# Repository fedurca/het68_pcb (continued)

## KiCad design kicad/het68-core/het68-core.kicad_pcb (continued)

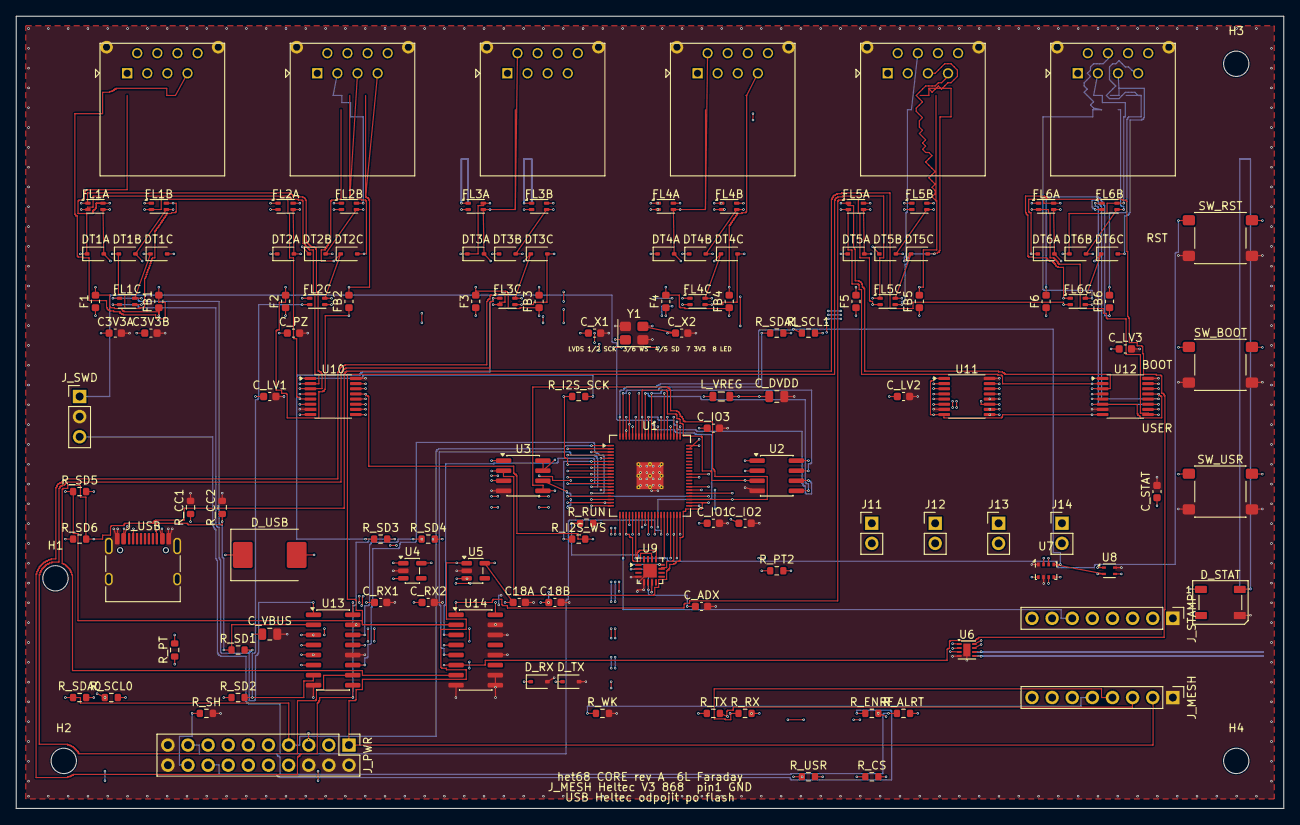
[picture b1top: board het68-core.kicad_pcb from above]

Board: 6 copper layers, 160.0 x 100.0 mm, 134 parts (0 on the bottom side), 156 nets.

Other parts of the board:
H1, H2, H3, H4: M3; MountingHole_3.2mm_M3

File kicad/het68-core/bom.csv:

Ref,Value,Footprint,MPN,LCSC
U1,RP2350B,Package_DFN_QFN:QFN-80-1EP_10x10mm_P0.4mm_EP3.4x3.4mm_ThermalVias,RP2350B,
U2,W25Q128JVSIQ,Package_SO:SOIC-8_3.9x4.9mm_P1.27mm,W25Q128JVSIQ,
U3,APS6404L,Package_SO:SOIC-8_3.9x4.9mm_P1.27mm,APS6404L-3SQR-SN,
Y1,12MHz,Crystal:Crystal_SMD_3225-4Pin_3.2x2.5mm,12MHz 3225,
C_X1,15p,Capacitor_SMD:C_0603_1608Metric,CL10C150JB8NNNC,
C_X2,15p,Capacitor_SMD:C_0603_1608Metric,CL10C150JB8NNNC,
L_VREG,2.2uH,Inductor_SMD:L_0805_2012Metric,2.2uH VREG,
C_DVDD,2.2u,Capacitor_SMD:C_0805_2012Metric,CL21A225KOQNNNE,
U4,AP2112K-3.3,Package_TO_SOT_SMD:SOT-23-5,AP2112K-3.3TRG1,
U5,AP2112K-1.8,Package_TO_SOT_SMD:SOT-23-5,AP2112K-1.8TRG1,C176944
C3V3A,1u,Capacitor_SMD:C_0603_1608Metric,CL10A105KA8NNNC,
C3V3B,100n,Capacitor_SMD:C_0603_1608Metric,CL10B104KB8NNNC,
C18A,1u,Capacitor_SMD:C_0603_1608Metric,CL10A105KA8NNNC,
C18B,100n,Capacitor_SMD:C_0603_1608Metric,CL10B104KB8NNNC,
R_RUN,10k,Resistor_SMD:R_0603_1608Metric,RC0603FR-0710KL,
R_WK,100k,Resistor_SMD:R_0603_1608Metric,RC0603FR-07100KL,
R_CS,10k,Resistor_SMD:R_0603_1608Metric,RC0603FR-0710KL,
R_USR,10k,Resistor_SMD:R_0603_1608Metric,RC0603FR-0710KL,
SW_RST,RESET,Button_Switch_SMD:SW_SPST_PTS645Sx43SMTR92,PTS645SM43SMTR92,
SW_BOOT,BOOT,Button_Switch_SMD:SW_SPST_PTS645Sx43SMTR92,PTS645SM43SMTR92,
SW_USR,USER,Button_Switch_SMD:SW_SPST_PTS645Sx43SMTR92,PTS645SM43SMTR92,
D_STAT,SK6812,LED_SMD:LED_WS2812B_PLCC4_5.0x5.0mm_P3.2mm,"SK6812 (5050, 3.3 V)",
C_STAT,100n,Capacitor_SMD:C_0603_1608Metric,CL10B104KB8NNNC,
J_USB,USB_C,Connector_USB:USB_C_Receptacle_HRO_TYPE-C-31-M-12,TYPE-C-31-M-12,C165948
R_CC1,5.1k,Resistor_SMD:R_0603_1608Metric,RC0603FR-075K1L,
R_CC2,5.1k,Resistor_SMD:R_0603_1608Metric,RC0603FR-075K1L,
D_USB,SS34,Diode_SMD:D_SMC,SS34,
C_VBUS,10u,Capacitor_SMD:C_0805_2012Metric,CL21A106KOQNNNE,
J_MESH,J_MESH,Connector_PinHeader_2.54mm:PinHeader_1x08_P2.54mm_Vertical,PinHeader 1x8 Heltec V3,
J_STAMP,J_STAMP_DNP,Connector_PinHeader_2.54mm:PinHeader_1x08_P2.54mm_Vertical,DNP stamp RAK class,
R_TX,22,Resistor_SMD:R_0603_1608Metric,RC0603FR-0722RL,
R_RX,22,Resistor_SMD:R_0603_1608Metric,RC0603FR-0722RL,
R_I2S_SCK,33,Resistor_SMD:R_0603_1608Metric,RC0603FR-0733RL,
R_I2S_WS,33,Resistor_SMD:R_0603_1608Metric,RC0603FR-0733RL,
D_TX,PESD5V0X1BT,Diode_SMD:D_SOD-323,PESD5V0X1BT,
D_RX,PESD5V0X1BT,Diode_SMD:D_SOD-323,PESD5V0X1BT,
J_SWD,SWD,Connector_PinHeader_2.54mm:PinHeader_1x03_P2.54mm_Vertical,SWD,
J_PWR,J_PWR,Connector_PinHeader_2.54mm:PinHeader_2x10_P2.54mm_Vertical,interconnect 2x10,
R_SDA0,4.7k,Resistor_SMD:R_0603_1608Metric,RC0603FR-074K7L,
R_SCL0,4.7k,Resistor_SMD:R_0603_1608Metric,RC0603FR-074K7L,
R_SDA1,4.7k,Resistor_SMD:R_0603_1608Metric,RC0603FR-074K7L,
R_SCL1,4.7k,Resistor_SMD:R_0603_1608Metric,RC0603FR-074K7L,
R_PT,1k,Resistor_SMD:R_0603_1608Metric,RC0603FR-071KL,
R_PT2,0,Resistor_SMD:R_0603_1608Metric,RC0603FR-070RL,
R_SH,0,Resistor_SMD:R_0603_1608Metric,RC0603FR-070RL,
R_ENRF,10k,Resistor_SMD:R_0603_1608Metric,RC0603FR-0710KL,
R_ALRT,10k,Resistor_SMD:R_0603_1608Metric,RC0603FR-0710KL,
U7,DPS310,Package_LGA:Bosch_LGA-8_2x2.5mm_P0.65mm_ClockwisePinNumbering,DPS310,C130156
U8,SHT40,Sensor_Humidity:Sensirion_DFN-4_1.5x1.5mm_P0.8mm_SHT4x_NoCentralPad,SHT40-AD1B-R2,C2909890
U9,ADXL355,Package_DFN_QFN:QFN-16-1EP_3x3mm_P0.5mm_EP1.7x1.7mm,ADXL355BCCZ,
C_ADX,100n,Capacitor_SMD:C_0603_1608Metric,CL10B104KB8NNNC,
U6,DRV8837C,Package_SON:Texas_DSG0008A_WSON-8-1EP_2x2mm_P0.5mm_EP0.9x1.6mm,DRV8837CDSGR,C191000
C_PZ,100n,Capacitor_SMD:C_0603_1608Metric,CL10B104KB8NNNC,
J11,PZ1,Connector_PinHeader_2.54mm:PinHeader_1x02_P2.54mm_Vertical,PS1240,
J12,PZ2,Connector_PinHeader_2.54mm:PinHeader_1x02_P2.54mm_Vertical,PS1240,
J13,PZ3,Connector_PinHeader_2.54mm:PinHeader_1x02_P2.54mm_Vertical,PS1240,
J14,PZ4,Connector_PinHeader_2.54mm:PinHeader_1x02_P2.54mm_Vertical,PS1240,
U10,SN65LVDS047,Package_SO:TSSOP-16_4.4x5mm_P0.65mm,SN65LVDS047PW,
C_LV1,100n,Capacitor_SMD:C_0603_1608Metric,CL10B104KB8NNNC,
U11,SN65LVDS047,Package_SO:TSSOP-16_4.4x5mm_P0.65mm,SN65LVDS047PW,
C_LV2,100n,Capacitor_SMD:C_0603_1608Metric,CL10B104KB8NNNC,
U12,SN65LVDS047,Package_SO:TSSOP-16_4.4x5mm_P0.65mm,SN65LVDS047PW,
C_LV3,100n,Capacitor_SMD:C_0603_1608Metric,CL10B104KB8NNNC,
U13,SN65LVDS32,Package_SO:SOIC-16_3.9x9.9mm_P1.27mm,SN65LVDS32D,
U14,SN65LVDS32,Package_SO:SOIC-16_3.9x9.9mm_P1.27mm,SN65LVDS32D,
C_RX1,100n,Capacitor_SMD:C_0603_1608Metric,CL10B104KB8NNNC,
C_RX2,100n,Capacitor_SMD:C_0603_1608Metric,CL10B104KB8NNNC,
J1,MIC1,het68:RJ45_Vertical_het68,RJ45-8P8C-VERT,
FL1A,CMC,Inductor_SMD:L_CommonModeChoke_Coilank_ACM2012,ACM2012,
FL1B,CMC,Inductor_SMD:L_CommonModeChoke_Coilank_ACM2012,ACM2012,
FL1C,CMC,Inductor_SMD:L_CommonModeChoke_Coilank_ACM2012,ACM2012,
DT1A,PESD5V0X1BT,Diode_SMD:D_SOD-323,PESD5V0X1BT,
DT1B,PESD5V0X1BT,Diode_SMD:D_SOD-323,PESD5V0X1BT,
DT1C,PESD5V0X1BT,Diode_SMD:D_SOD-323,PESD5V0X1BT,
R_SD1,100,Resistor_SMD:R_0603_1608Metric,RC0603FR-07100RL,
F1,0.25A,Fuse:Fuse_0603_1608Metric,PPTC 0603,
FB1,600R,Inductor_SMD:L_0603_1608Metric,BLM18PG601SN1D,
J2,MIC2,het68:RJ45_Vertical_het68,RJ45-8P8C-VERT,
FL2A,CMC,Inductor_SMD:L_CommonModeChoke_Coilank_ACM2012,ACM2012,
FL2B,CMC,Inductor_SMD:L_CommonModeChoke_Coilank_ACM2012,ACM2012,
FL2C,CMC,Inductor_SMD:L_CommonModeChoke_Coilank_ACM2012,ACM2012,
DT2A,PESD5V0X1BT,Diode_SMD:D_SOD-323,PESD5V0X1BT,
DT2B,PESD5V0X1BT,Diode_SMD:D_SOD-323,PESD5V0X1BT,
DT2C,PESD5V0X1BT,Diode_SMD:D_SOD-323,PESD5V0X1BT,
R_SD2,100,Resistor_SMD:R_0603_1608Metric,RC0603FR-07100RL,
F2,0.25A,Fuse:Fuse_0603_1608Metric,PPTC 0603,
FB2,600R,Inductor_SMD:L_0603_1608Metric,BLM18PG601SN1D,
J3,MIC3,het68:RJ45_Vertical_het68,RJ45-8P8C-VERT,
FL3A,CMC,Inductor_SMD:L_CommonModeChoke_Coilank_ACM2012,ACM2012,
FL3B,CMC,Inductor_SMD:L_CommonModeChoke_Coilank_ACM2012,ACM2012,
FL3C,CMC,Inductor_SMD:L_CommonModeChoke_Coilank_ACM2012,ACM2012,
DT3A,PESD5V0X1BT,Diode_SMD:D_SOD-323,PESD5V0X1BT,
DT3B,PESD5V0X1BT,Diode_SMD:D_SOD-323,PESD5V0X1BT,
DT3C,PESD5V0X1BT,Diode_SMD:D_SOD-323,PESD5V0X1BT,
R_SD3,100,Resistor_SMD:R_0603_1608Metric,RC0603FR-07100RL,
F3,0.25A,Fuse:Fuse_0603_1608Metric,PPTC 0603,
FB3,600R,Inductor_SMD:L_0603_1608Metric,BLM18PG601SN1D,
J4,MIC4,het68:RJ45_Vertical_het68,RJ45-8P8C-VERT,
FL4A,CMC,Inductor_SMD:L_CommonModeChoke_Coilank_ACM2012,ACM2012,
FL4B,CMC,Inductor_SMD:L_CommonModeChoke_Coilank_ACM2012,ACM2012,
FL4C,CMC,Inductor_SMD:L_CommonModeChoke_Coilank_ACM2012,ACM2012,
DT4A,PESD5V0X1BT,Diode_SMD:D_SOD-323,PESD5V0X1BT,
DT4B,PESD5V0X1BT,Diode_SMD:D_SOD-323,PESD5V0X1BT,
DT4C,PESD5V0X1BT,Diode_SMD:D_SOD-323,PESD5V0X1BT,
R_SD4,100,Resistor_SMD:R_0603_1608Metric,RC0603FR-07100RL,
F4,0.25A,Fuse:Fuse_0603_1608Metric,PPTC 0603,
FB4,600R,Inductor_SMD:L_0603_1608Metric,BLM18PG601SN1D,
J5,MIC5,het68:RJ45_Vertical_het68,RJ45-8P8C-VERT,
FL5A,CMC,Inductor_SMD:L_CommonModeChoke_Coilank_ACM2012,ACM2012,
FL5B,CMC,Inductor_SMD:L_CommonModeChoke_Coilank_ACM2012,ACM2012,
FL5C,CMC,Inductor_SMD:L_CommonModeChoke_Coilank_ACM2012,ACM2012,
DT5A,PESD5V0X1BT,Diode_SMD:D_SOD-323,PESD5V0X1BT,
DT5B,PESD5V0X1BT,Diode_SMD:D_SOD-323,PESD5V0X1BT,
DT5C,PESD5V0X1BT,Diode_SMD:D_SOD-323,PESD5V0X1BT,
R_SD5,100,Resistor_SMD:R_0603_1608Metric,RC0603FR-07100RL,
F5,0.25A,Fuse:Fuse_0603_1608Metric,PPTC 0603,
FB5,600R,Inductor_SMD:L_0603_1608Metric,BLM18PG601SN1D,
J6,MIC6,het68:RJ45_Vertical_het68,RJ45-8P8C-VERT,
FL6A,CMC,Inductor_SMD:L_CommonModeChoke_Coilank_ACM2012,ACM2012,
FL6B,CMC,Inductor_SMD:L_CommonModeChoke_Coilank_ACM2012,ACM2012,
FL6C,CMC,Inductor_SMD:L_CommonModeChoke_Coilank_ACM2012,ACM2012,
DT6A,PESD5V0X1BT,Diode_SMD:D_SOD-323,PESD5V0X1BT,
DT6B,PESD5V0X1BT,Diode_SMD:D_SOD-323,PESD5V0X1BT,
DT6C,PESD5V0X1BT,Diode_SMD:D_SOD-323,PESD5V0X1BT,
R_SD6,100,Resistor_SMD:R_0603_1608Metric,RC0603FR-07100RL,
F6,0.25A,Fuse:Fuse_0603_1608Metric,PPTC 0603,
FB6,600R,Inductor_SMD:L_0603_1608Metric,BLM18PG601SN1D,
C_IO1,100n,Capacitor_SMD:C_0603_1608Metric,CL10B104KB8NNNC,
C_IO2,100n,Capacitor_SMD:C_0603_1608Metric,CL10B104KB8NNNC,
C_IO3,1u,Capacitor_SMD:C_0603_1608Metric,CL10A105KA8NNNC,

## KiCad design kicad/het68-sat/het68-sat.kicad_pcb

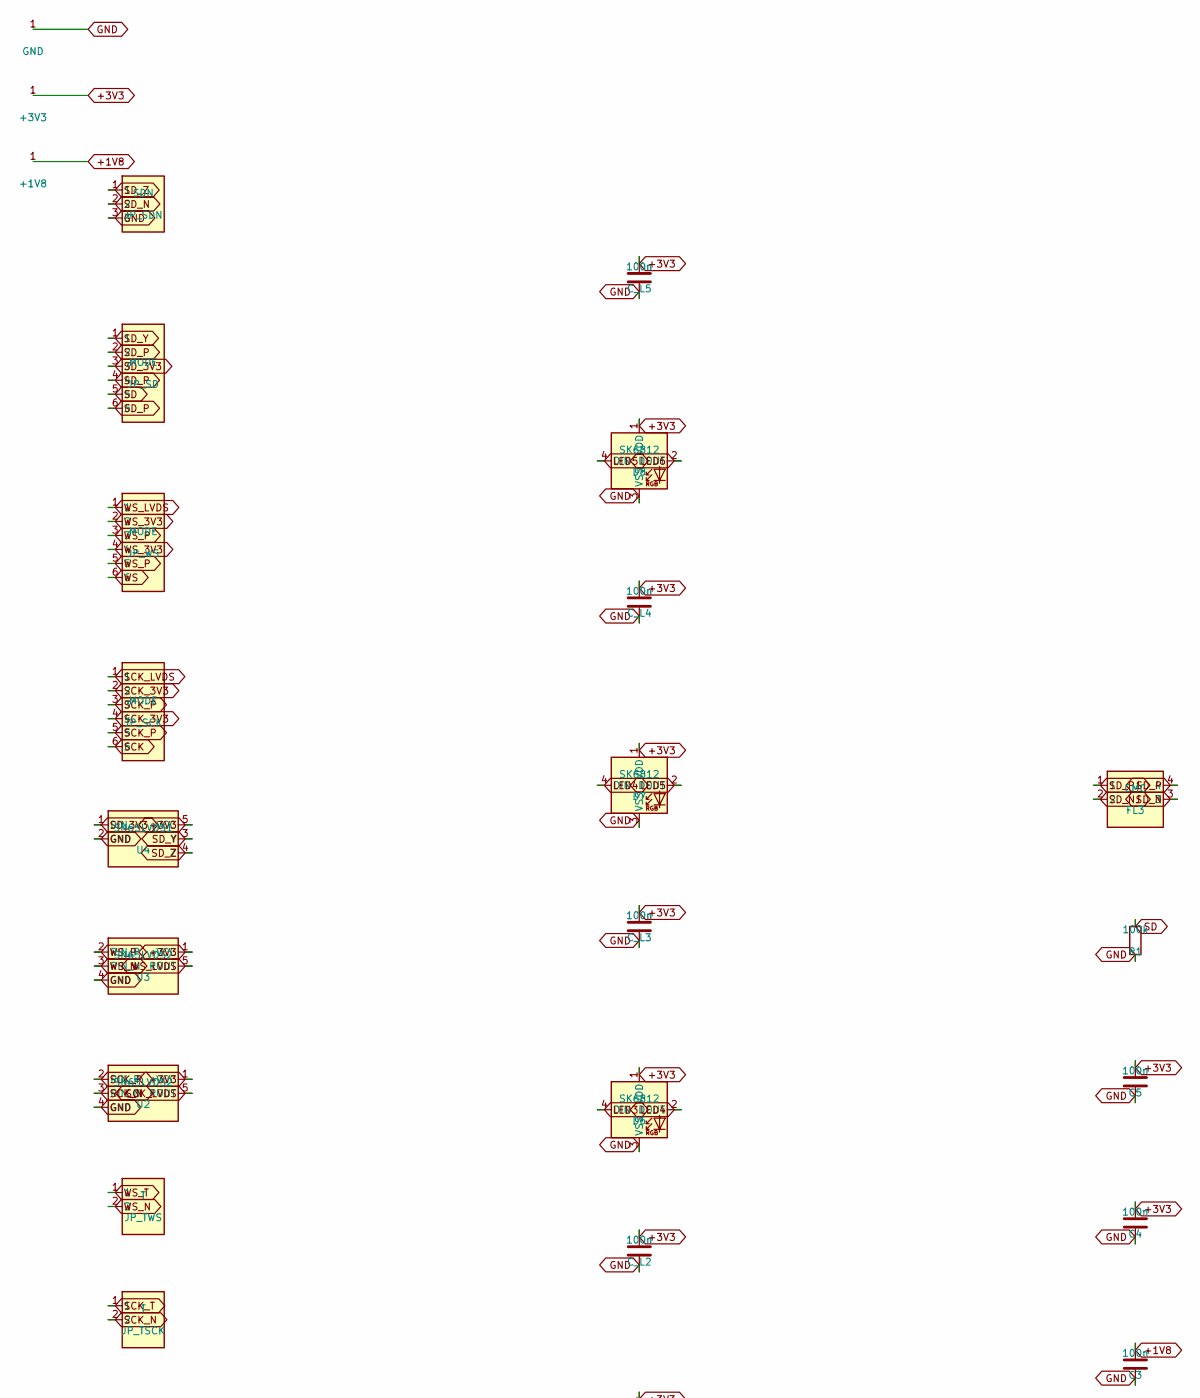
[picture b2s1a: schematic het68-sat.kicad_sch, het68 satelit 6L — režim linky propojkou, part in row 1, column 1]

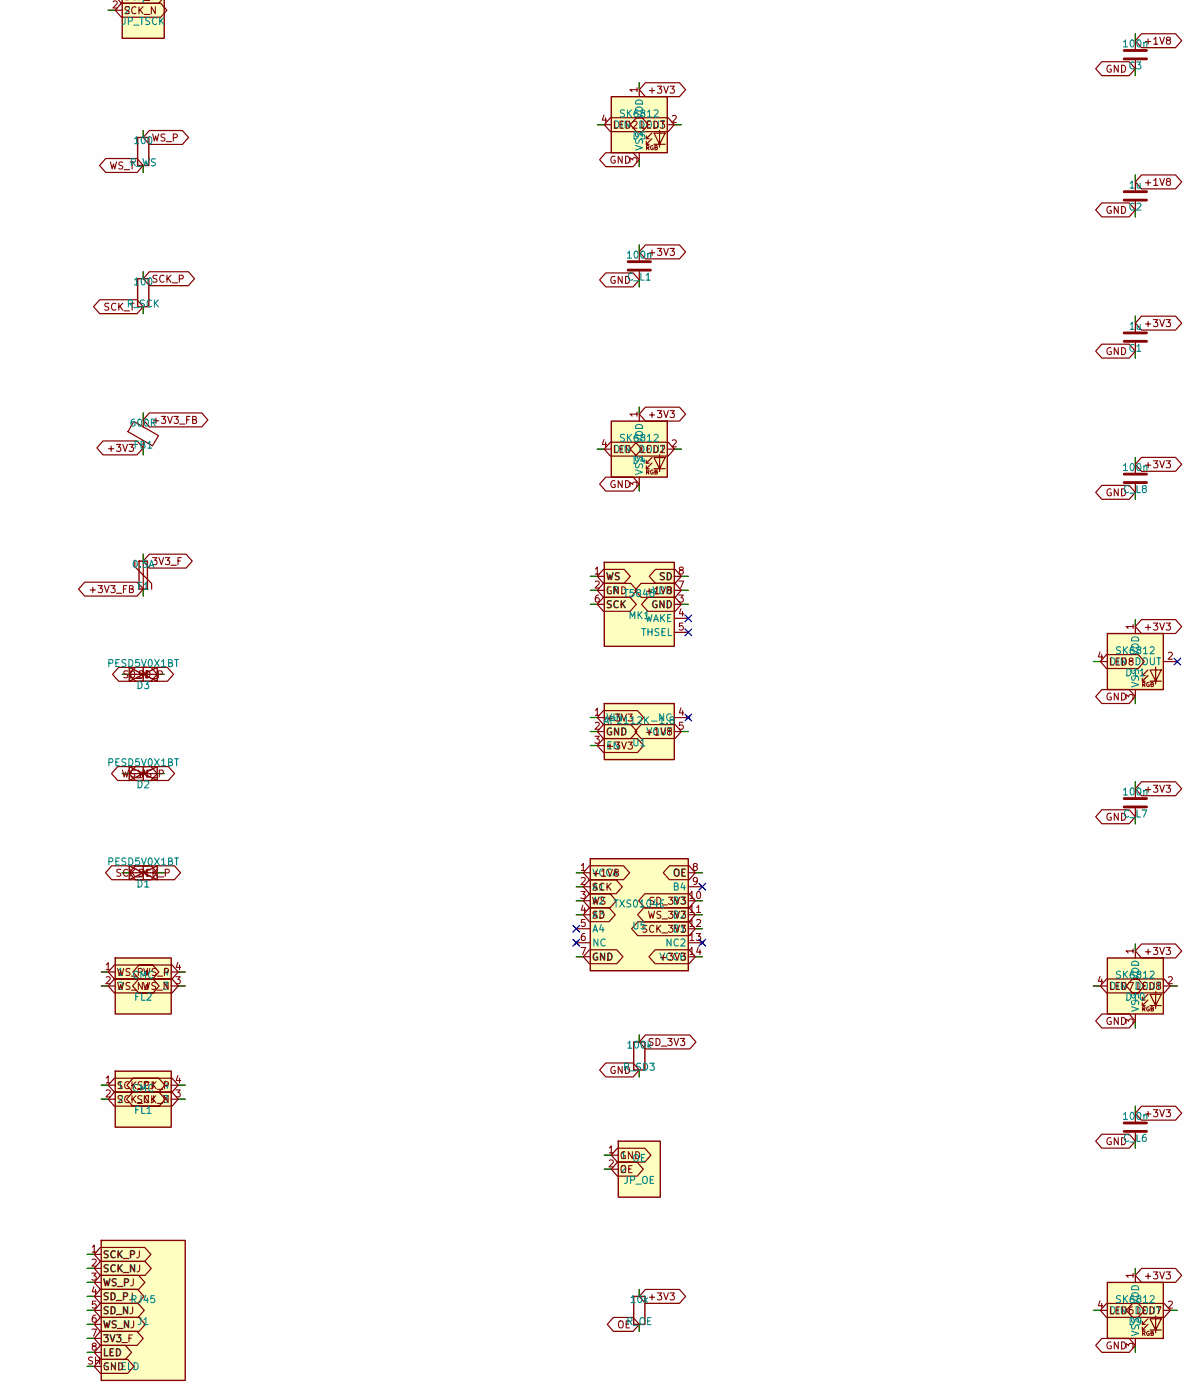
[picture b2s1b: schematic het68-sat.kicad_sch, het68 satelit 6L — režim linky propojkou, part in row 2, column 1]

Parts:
C1, C2: 1u; C_0603_1608Metric; MPN CL10A105KA8NNNC
C3, C4, C5: 100n; C_0603_1608Metric; MPN CL10B104KB8NNNC
C_L1, C_L2, C_L3, C_L4, C_L5, C_L6, C_L7, C_L8: 100n; C_0603_1608Metric; MPN CL10B104KB8NNNC
D1, D2, D3: PESD5V0X1BT; D_SOD-323; MPN PESD5V0X1BT
D4, D5, D6, D7, D8, D9, D10, D11: SK6812; LED_WS2812B_PLCC4_5.0x5.0mm_P3.2mm; MPN SK6812 (5050, 3.3 V)
F1: 0.5A; Fuse_0603_1608Metric; MPN PPTC 0603
FB1: 600R; L_0603_1608Metric; MPN BLM18PG601SN1D
FL1, FL2, FL3: CMC; L_CommonModeChoke_Coilank_ACM2012; MPN ACM2012
J1: RJ45; RJ45_Vertical_het68; MPN RJ45-8P8C-VERT
JP_OE: OE; PinHeader_1x02_P2.54mm_Vertical; MPN jumper OE to GND = 1V8 mode
JP_SCK: MODE; PinHeader_2x03_P2.54mm_Vertical; MPN SCK radky DIFF / 3V3 / 1V8
JP_SD: MODE; PinHeader_2x03_P2.54mm_Vertical; MPN SD radky DIFF / 3V3 / 1V8
JP_SDN: SDN; PinHeader_1x03_P2.54mm_Vertical; MPN jumper SDN 1-2 DIFF 2-3 single-ended
JP_TSCK: T; PinHeader_1x02_P2.54mm_Vertical; MPN jumper DIFF term SCK
JP_TWS: T; PinHeader_1x02_P2.54mm_Vertical; MPN jumper DIFF term WS
JP_WS: MODE; PinHeader_2x03_P2.54mm_Vertical; MPN WS radky DIFF / 3V3 / 1V8
MK1: T5848; MPN MMICT5848-00-012
R1: 100k; R_0603_1608Metric; MPN RC0603FR-07100KL
R_OE: 10k; R_0603_1608Metric; MPN RC0603FR-0710KL
R_SCK: 100; R_0603_1608Metric; MPN RC0603FR-07100RL
R_SD3: 100k; R_0603_1608Metric; MPN RC0603FR-07100KL
R_WS: 100; R_0603_1608Metric; MPN RC0603FR-07100RL
U1: AP2112K-1.8; SOT-23-5; MPN AP2112K-1.8TRG1
U2, U3: SN65LVDS2; SOT-23-5; MPN SN65LVDS2DBVR
U4: SN65LVDS1; SOT-23-5; MPN SN65LVDS1DBVR
U5: TXS0104E; SOIC-14_3.9x8.7mm_P1.27mm; MPN TXS0104EDR

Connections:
3V3_F: F1.1, J1.7 (3V3)
+1V8: C2.1, C3.1, MK1.7 (VDD), U1.5 (VOUT), U5.1 (VCCA)
+3V3: C1.1, C4.1, C5.1, C_L1.1, C_L2.1, C_L3.1, C_L4.1, C_L5.1, C_L6.1, C_L7.1, C_L8.1, D4.1 (VDD), D5.1 (VDD), D6.1 (VDD), D7.1 (VDD), D8.1 (VDD), D9.1 (VDD), D10.1 (VDD), D11.1 (VDD), FB1.2, R_OE.1, U1.1 (VIN), U1.3 (EN), U2.1 (VCC), U3.1 (VCC), U4.5 (VCC), U5.14 (VCCB)
+3V3_FB: F1.2, FB1.1
GND: C1.2, C2.2, C3.2, C4.2, C5.2, C_L1.2, C_L2.2, C_L3.2, C_L4.2, C_L5.2, C_L6.2, C_L7.2, C_L8.2, D4.3 (VSS), D5.3 (VSS), D6.3 (VSS), D7.3 (VSS), D8.3 (VSS), D9.3 (VSS), D10.3 (VSS), D11.3 (VSS), J1.SH (SHIELD), JP_OE.1, JP_SDN.3, MK1.2 (LR), MK1.3 (GND), R1.2, R_SD3.2, U1.2 (GND), U2.4 (GND), U3.4 (GND), U4.2 (GND), U5.7 (GND)
LED: D4.4 (DIN), J1.8 (LED)
LED2: D4.2 (DOUT), D5.4 (DIN)
LED3: D5.2 (DOUT), D6.4 (DIN)
LED4: D6.2 (DOUT), D7.4 (DIN)
LED5: D7.2 (DOUT), D8.4 (DIN)
LED6: D8.2 (DOUT), D9.4 (DIN)
LED7: D9.2 (DOUT), D10.4 (DIN)
LED8: D10.2 (DOUT), D11.4 (DIN)
OE: JP_OE.2, R_OE.2, U5.8 (OE)
SCK: JP_SCK.6, MK1.6 (SCK), U5.2 (A1)
SCK_3V3: JP_SCK.2, JP_SCK.4, U5.12 (B1)
SCK_LVDS: JP_SCK.1, U2.5 (ROUT)
SCK_N: D1.2 (A2), FL1.3, JP_TSCK.2, U2.3 (RIN_N)
SCK_NJ: FL1.2, J1.2 (SCK_N)
SCK_P: D1.1 (A1), FL1.4, JP_SCK.3, JP_SCK.5, R_SCK.1, U2.2 (RIN_P)
SCK_PJ: FL1.1, J1.1 (SCK_P)
SCK_T: JP_TSCK.1, R_SCK.2
SD: JP_SD.5, MK1.8 (SD), R1.1, U5.4 (A3)
SD_3V3: JP_SD.3, R_SD3.1, U4.1 (DIN), U5.10 (B3)
SD_N: D3.2 (A2), FL3.3, JP_SDN.2
SD_NJ: FL3.2, J1.5 (SD_N)
SD_P: D3.1 (A1), FL3.4, JP_SD.2, JP_SD.4, JP_SD.6
SD_PJ: FL3.1, J1.4 (SD_P)
SD_Y: JP_SD.1, U4.3 (Y)
SD_Z: JP_SDN.1, U4.4 (Z)
WS: JP_WS.6, MK1.1 (WS), U5.3 (A2)
WS_3V3: JP_WS.2, JP_WS.4, U5.11 (B2)
WS_LVDS: JP_WS.1, U3.5 (ROUT)
WS_N: D2.2 (A2), FL2.3, JP_TWS.2, U3.3 (RIN_N)
WS_NJ: FL2.2, J1.6 (WS_N)
WS_P: D2.1 (A1), FL2.4, JP_WS.3, JP_WS.5, R_WS.1, U3.2 (RIN_P)
WS_PJ: FL2.1, J1.3 (WS_P)
WS_T: JP_TWS.1, R_WS.2

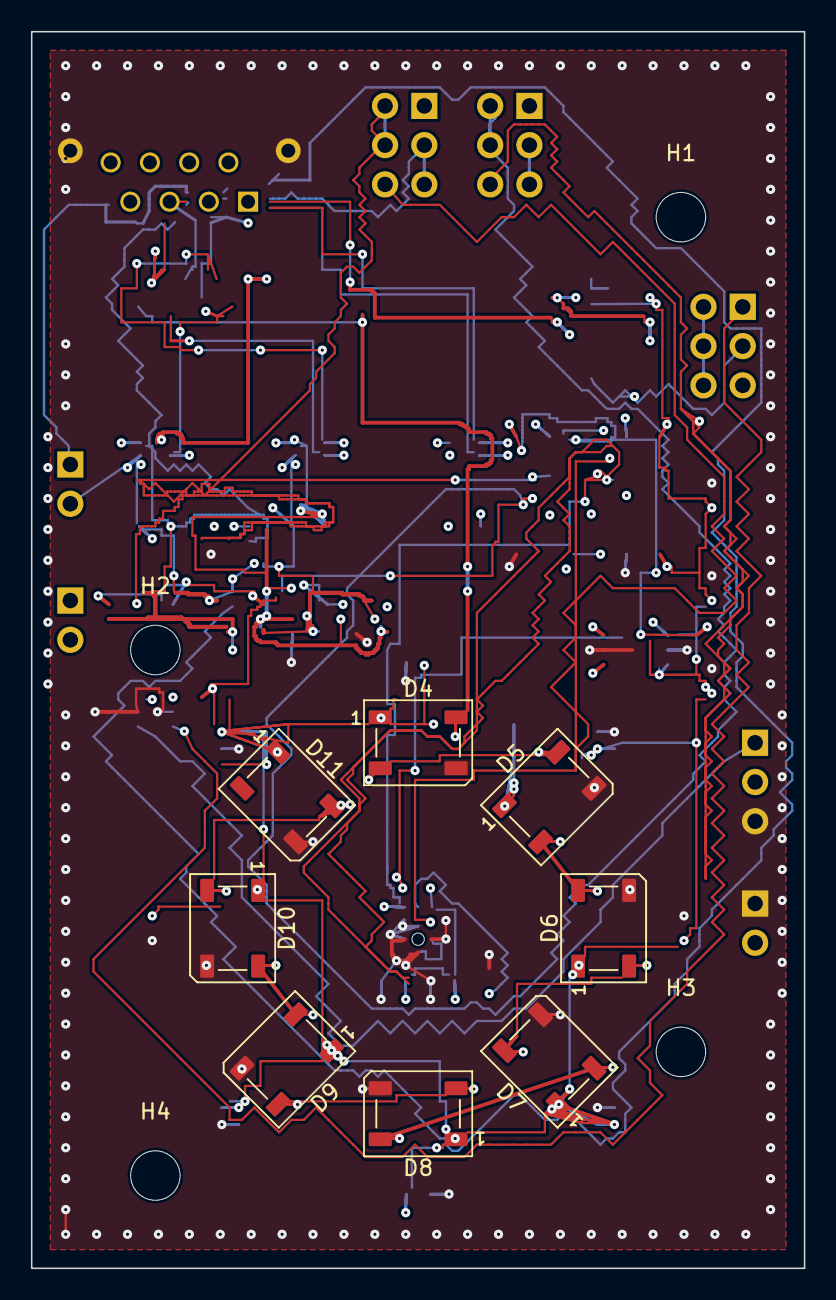
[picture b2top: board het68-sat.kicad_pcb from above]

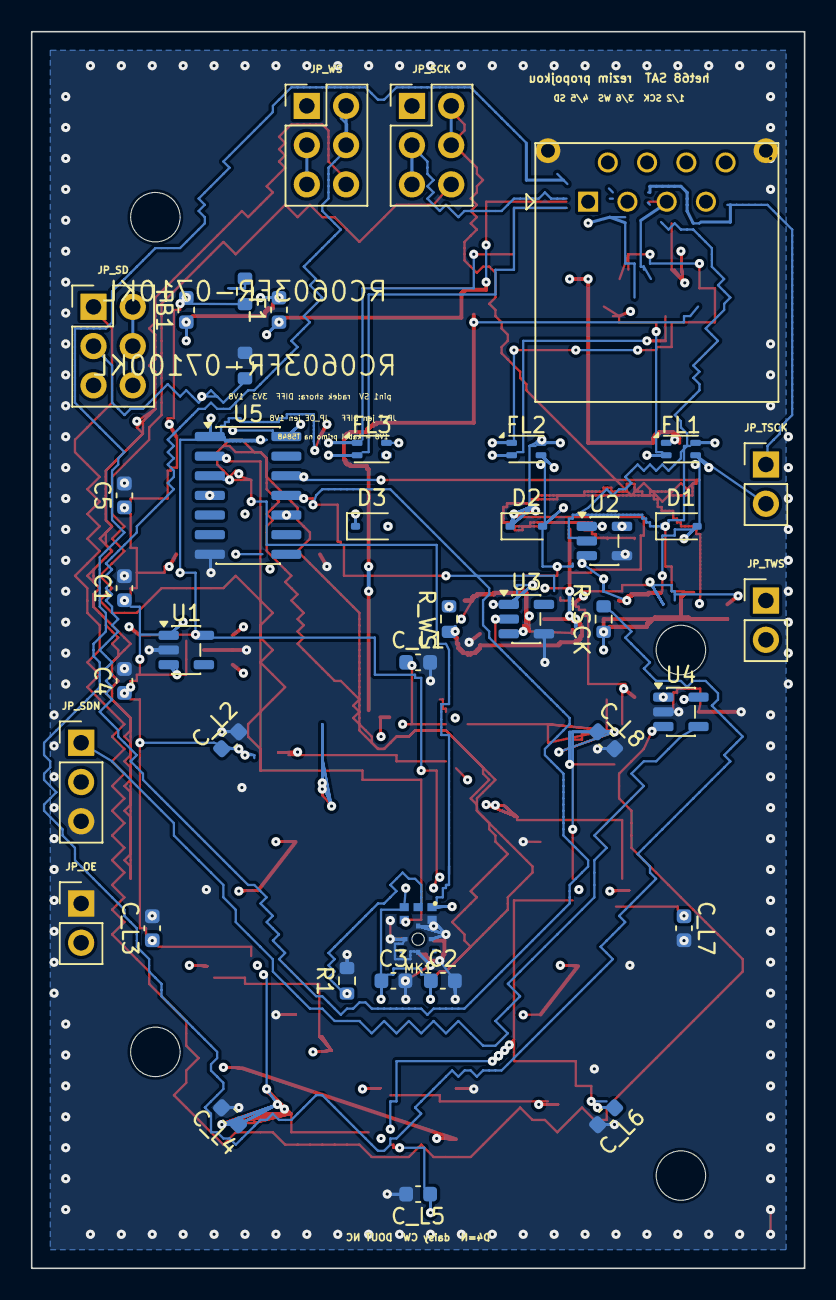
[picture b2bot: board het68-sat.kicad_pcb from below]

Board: 6 copper layers, 50.0 x 80.0 mm, 52 parts (40 on the bottom side), 38 nets.

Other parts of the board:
H1, H2, H3, H4: M3; MountingHole_3.2mm_M3

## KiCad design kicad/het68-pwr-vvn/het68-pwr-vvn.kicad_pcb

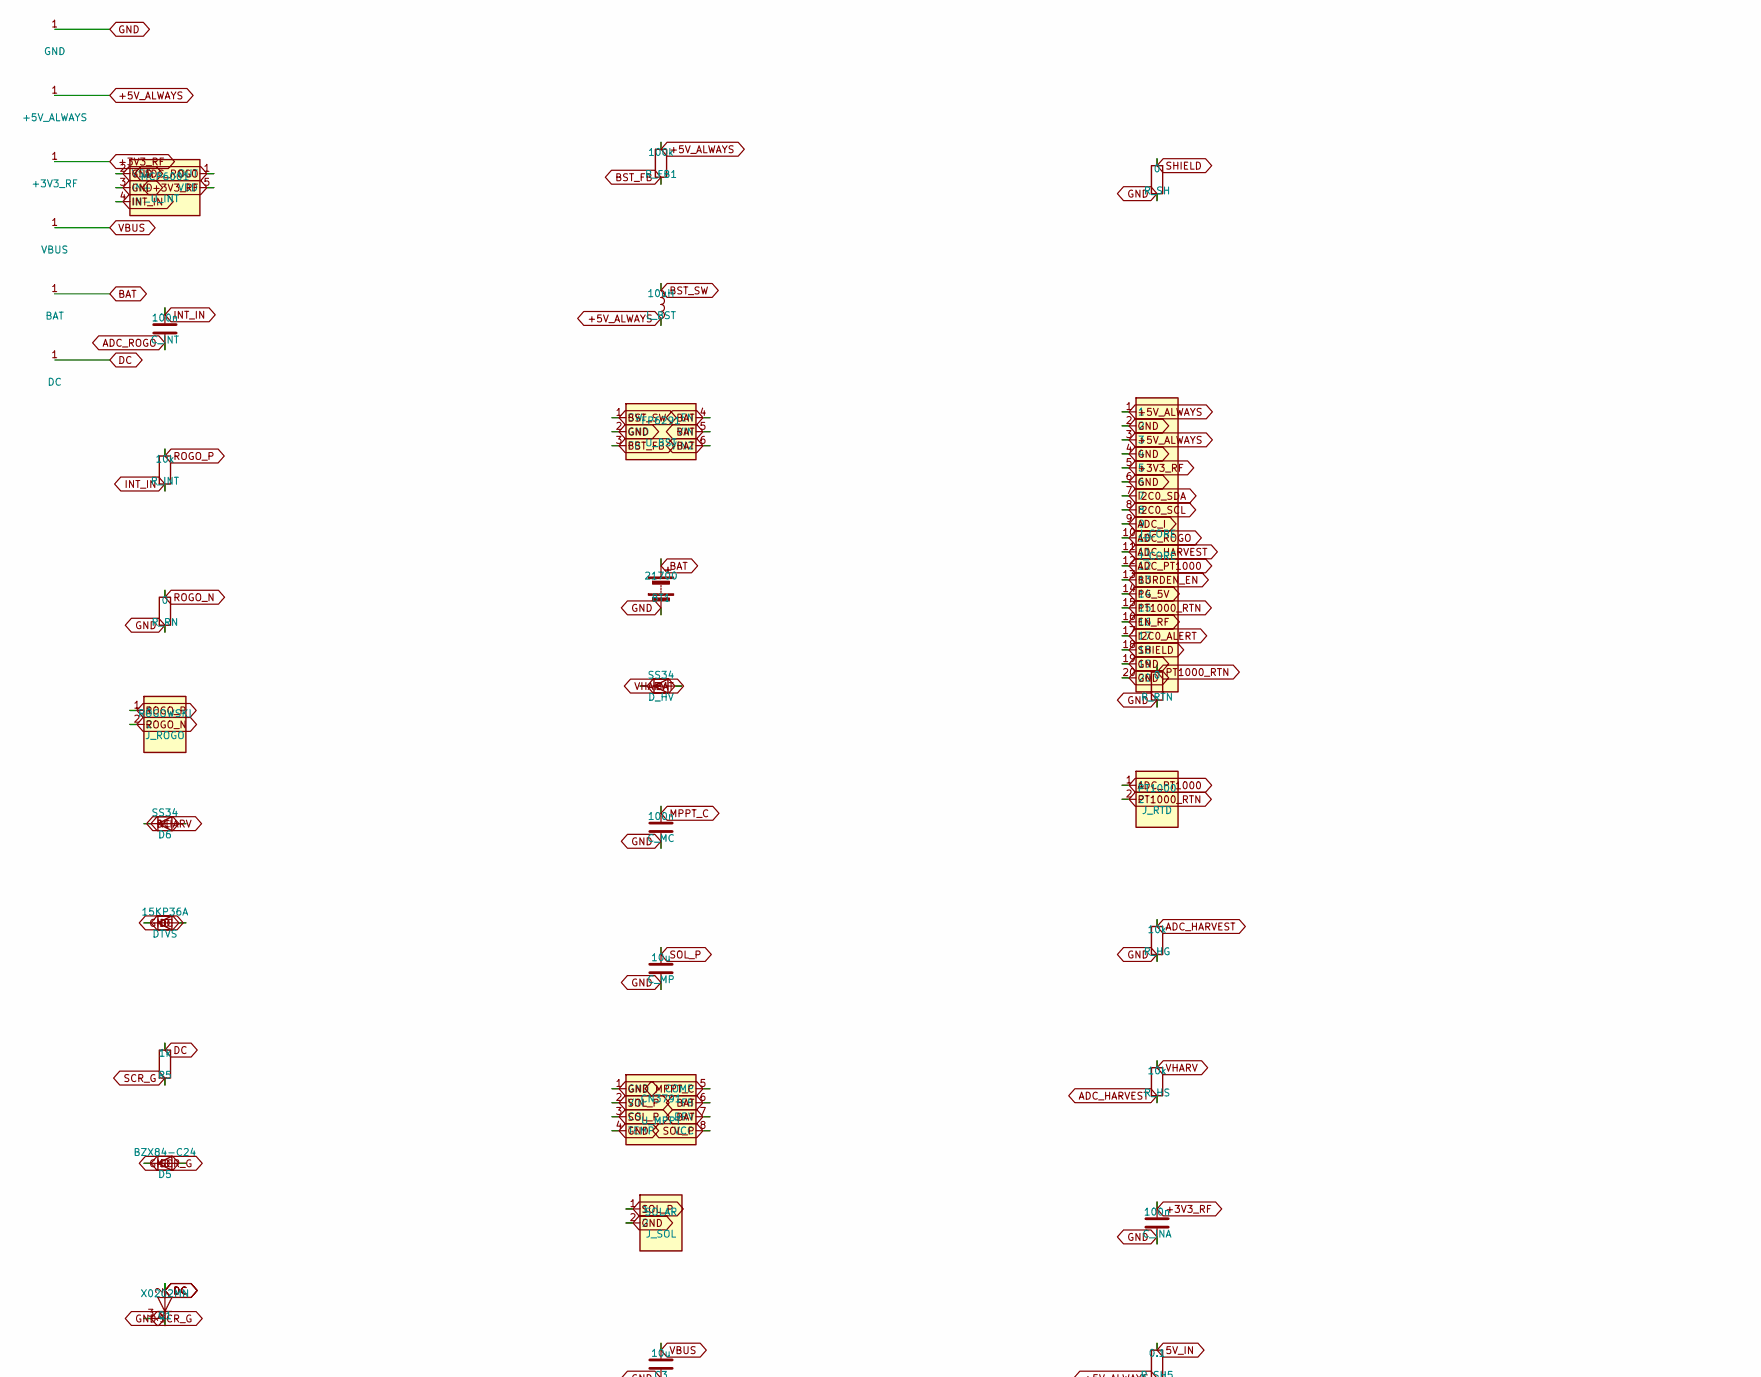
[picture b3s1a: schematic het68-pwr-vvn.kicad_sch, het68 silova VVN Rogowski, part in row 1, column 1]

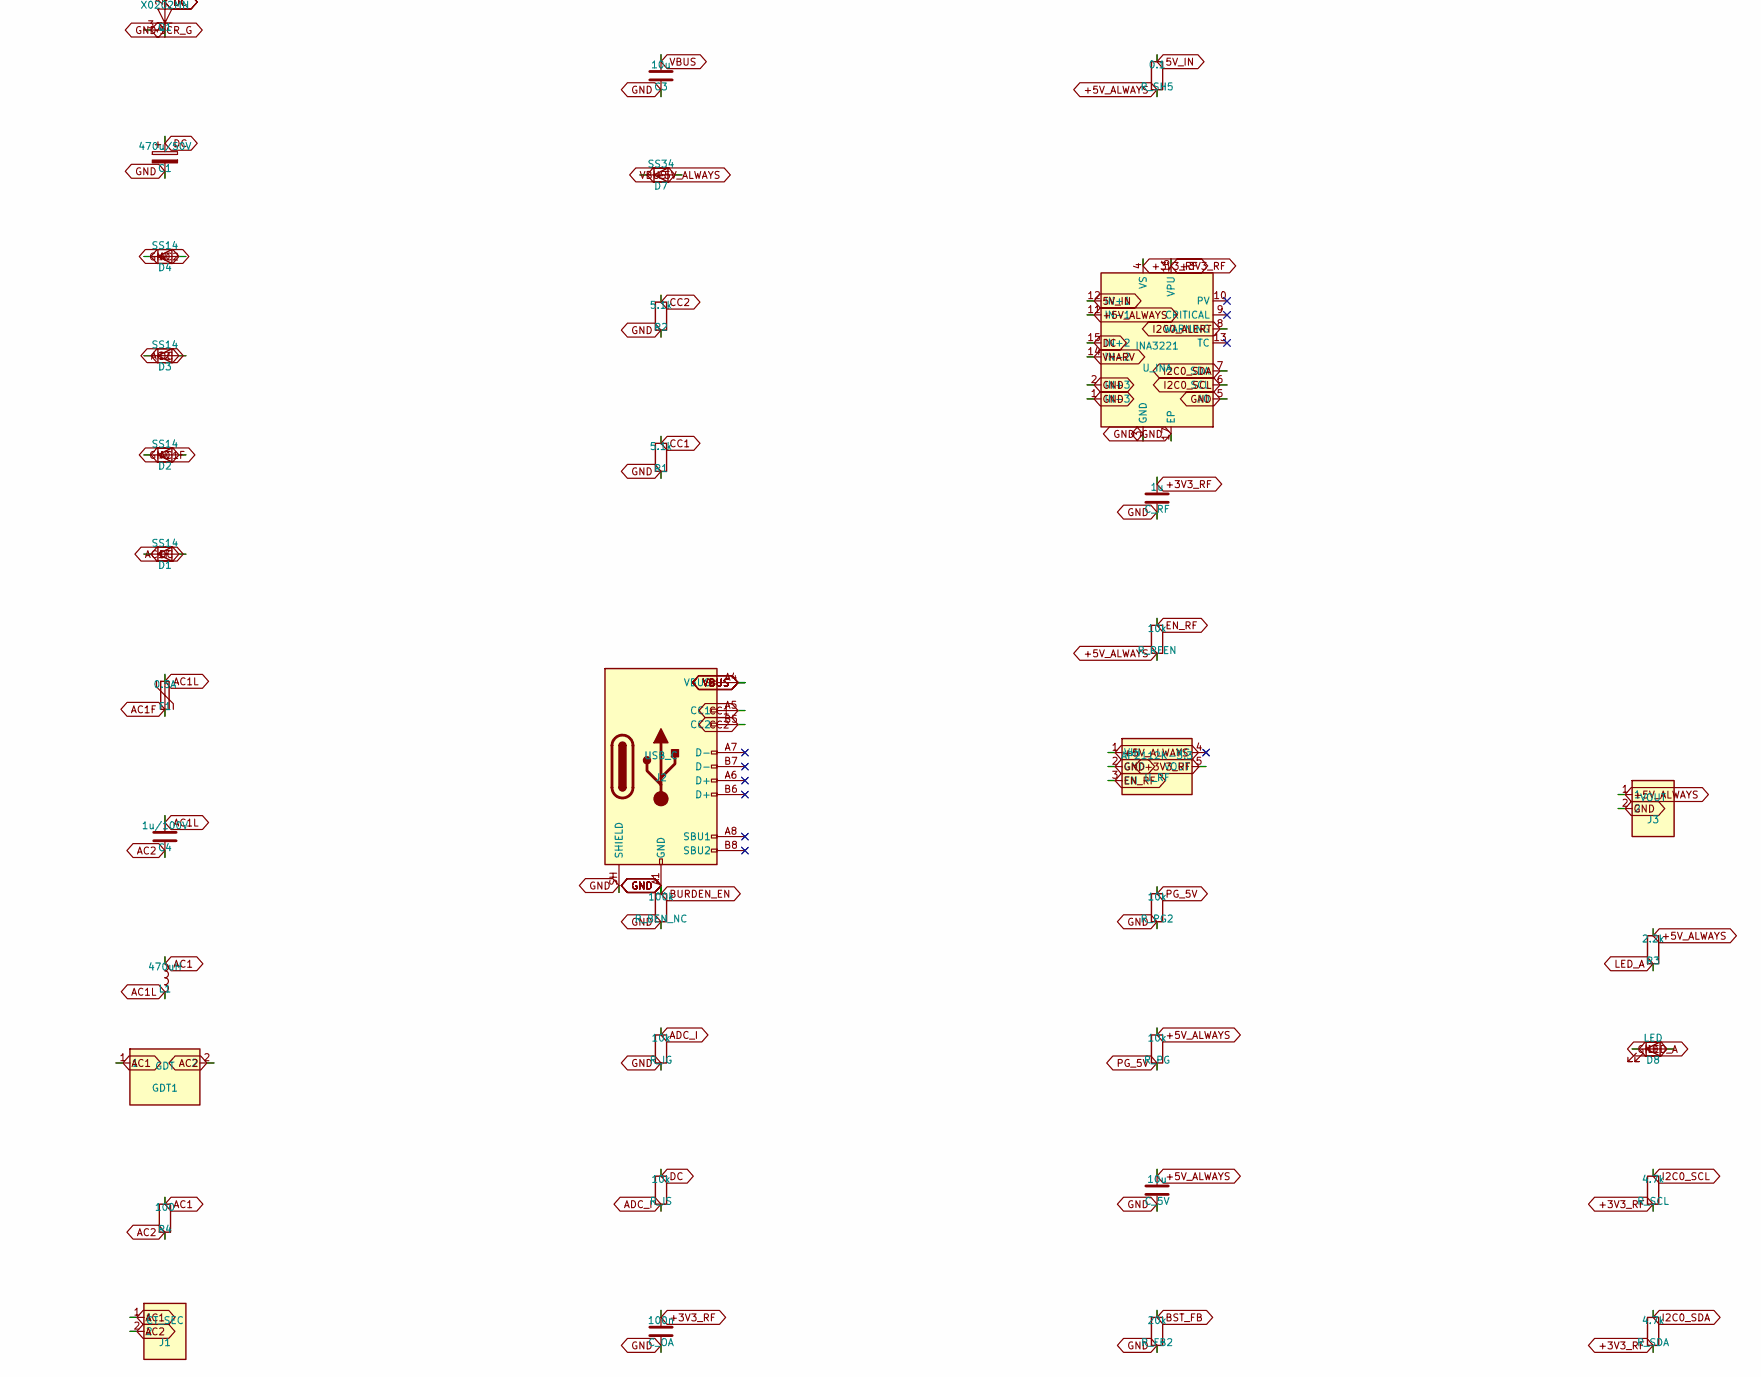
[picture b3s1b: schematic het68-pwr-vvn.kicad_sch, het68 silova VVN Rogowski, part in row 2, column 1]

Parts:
BT1: 21700; Keystone_1122_21700; MPN Keystone 1122
C1: 470u/50V; CP_Radial_D10.0mm_P5.00mm; MPN electrolytic 470u 50V
C3: 10u; C_0805_2012Metric; MPN CL21A106KOQNNNE
C4: 1u/100V; C_1206_3216Metric; MPN 1uF 100V X7R LC
C_5V: 10u; C_0805_2012Metric; MPN CL21A106KOQNNNE
C_INA: 100n; C_0603_1608Metric; MPN CL10B104KB8NNNC
C_INT: 100n; C_0603_1608Metric; MPN CL10B104KB8NNNC
C_MC: 100n; C_0603_1608Metric; MPN CL10B104KB8NNNC
C_MP: 10u; C_0805_2012Metric; MPN CL21A106KOQNNNE
C_OA: 100n; C_0603_1608Metric; MPN CL10B104KB8NNNC
C_RF: 1u; C_0603_1608Metric; MPN CL10A105KA8NNNC
D1, D2, D3, D4: SS14; D_SMA; MPN SS14
D5: BZX84-C24; D_SOD-323; MPN BZX84-C24
D6, D7: SS34; D_SMC; MPN SS34
D8: LED; LED_0603_1608Metric; MPN LED 0603
DTVS: 15KP36A; D_DO-201_P15.24mm_Horizontal; MPN 15KP36A
D_HV: SS34; D_SMC; MPN SS34
F1: 0.5A; Fuse_1812_4532Metric; MPN polyfuse 1812 0.5 A
GDT1: GDT; Fuse_1812_4532Metric; MPN GDT secondary
J1: CT_SEC; PinHeader_1x02_P2.54mm_Vertical; MPN sekundar CT, NE sit
J2: USB_C; USB_C_Receptacle_HRO_TYPE-C-31-M-12; MPN TYPE-C-31-M-12
J3: VOUT; PinHeader_1x02_P2.54mm_Vertical; MPN 5V lab
J_CORE: J_CORE; PinHeader_2x10_P2.54mm_Vertical; MPN interconnect 2x10
J_ROGO: ROGOWSKI; PinHeader_1x02_P2.54mm_Vertical; MPN Rogowski secondary, NE sit
J_RTD: PT1000; PinHeader_1x02_P2.54mm_Vertical; MPN PT1000 on conductor
J_SOL: SOLAR; PinHeader_1x02_P2.54mm_Vertical; MPN panel Voc 6-18 V
L1: 470uH; L_Radial_D10.0mm_P5.00mm_Fastron_07P; MPN 470uH radial
L_BST: 10uH; L_0805_2012Metric; MPN 10uH boost
Q1: X0202MN; SOT-223; MPN X0202MN
R1, R2: 5.1k; R_0603_1608Metric; MPN RC0603FR-075K1L
R3: 2.2k; R_0603_1608Metric; MPN RC0603FR-072K2L
R4: 100; R_Axial_DIN0207_L6.3mm_D2.5mm_P10.16mm_Horizontal; MPN 100R THT burden
R5: 1k; R_0805_2012Metric; MPN RC0805FR-071KL
R_BEN_NC: 100k; R_0603_1608Metric; MPN RC0603FR-07100KL
R_FB1: 100k; R_0603_1608Metric; MPN RC0603FR-07100KL
R_FB2: 20k; R_0603_1608Metric; MPN RC0603FR-0720KL
R_HG: 10k; R_0603_1608Metric; MPN RC0603FR-0710KL
R_HS: 10k; R_0603_1608Metric; MPN RC0603FR-0710KL
R_IG: 10k; R_0603_1608Metric; MPN RC0603FR-0710KL
R_INT: 10k; R_0603_1608Metric; MPN RC0603FR-0710KL
R_IS: 10k; R_0603_1608Metric; MPN RC0603FR-0710KL
R_PG, R_PG2: 10k; R_0603_1608Metric; MPN RC0603FR-0710KL
R_RFEN: 10k; R_0603_1608Metric; MPN RC0603FR-0710KL
R_RN: 0; R_0603_1608Metric; MPN RC0603FR-070RL
R_RTN: 0; R_0603_1608Metric; MPN RC0603FR-070RL
R_SCL: 4.7k; R_0603_1608Metric; MPN RC0603FR-074K7L
R_SDA: 4.7k; R_0603_1608Metric; MPN RC0603FR-074K7L
R_SH: 0; R_0603_1608Metric; MPN RC0603FR-070RL
R_SH5: 0.1; R_0805_2012Metric; MPN RC0805FR-070R1L
U_BST: FP6291; SOT-23-6; MPN FP6291
U_INA: INA3221; Texas_RGV0016A_VQFN-16-1EP_4x4mm_P0.65mm_EP2.1x2.1mm; MPN INA3221AIRGVR
U_INT: MCP6001; SOT-23-5; MPN MCP6001T-OT
U_MPPT: CN3791; SOIC-8_3.9x4.9mm_P1.27mm; MPN CN3791
U_RF: AP2112K-3.3; SOT-23-5; MPN AP2112K-3.3TRG1

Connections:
5V_IN: R_SH5.1, U_INA.12 (IN+1)
+3V3_RF: C_INA.1, C_OA.1, C_RF.1, J_CORE.5, R_SCL.2, R_SDA.2, U_INA.4 (VS), U_INA.16 (VPU), U_INT.5 (VDD), U_RF.5 (VOUT)
+5V_ALWAYS: C_5V.1, D7.1 (K), J3.1, J_CORE.1, J_CORE.3, L_BST.2, R3.1, R_FB1.1, R_PG.1, R_RFEN.2, R_SH5.2, U_INA.11 (IN-1), U_RF.1 (VIN)
AC1: GDT1.1, J1.1, L1.1, R4.1
AC1F: D1.2 (A), D2.1 (K), F1.2
AC1L: C4.1, F1.1, L1.2
AC2: C4.2, D3.2 (A), D4.1 (K), GDT1.2, J1.2, R4.2
ADC_HARVEST: J_CORE.11, R_HG.1, R_HS.2
ADC_I: J_CORE.9, R_IG.1, R_IS.2
ADC_PT1000: J_CORE.12, J_RTD.1
ADC_ROGO: C_INT.2, J_CORE.10, U_INT.1 (OUT)
BAT: BT1.1 (+), D_HV.1 (K), U_BST.4 (EN), U_BST.5 (VIN), U_BST.6 (VIN2), U_MPPT.6 (FB), U_MPPT.7 (DRV)
BST_FB: R_FB1.2, R_FB2.1, U_BST.3 (FB)
BST_SW: L_BST.1, U_BST.1 (SW)
BURDEN_EN: J_CORE.13, R_BEN_NC.1
CC1: J2.A5 (CC1), R1.1
CC2: J2.B5 (CC2), R2.1
DC: C1.1, D1.1 (K), D3.1 (K), D6.2 (A), DTVS.1 (K), Q1.2 (A), Q1.4 (A), R5.1, R_IS.1, U_INA.15 (IN+2)
EN_RF: J_CORE.16, R_RFEN.1, U_RF.3 (EN)
GND: BT1.2 (-), C1.2, C3.2, C_5V.2, C_INA.2, C_MC.2, C_MP.2, C_OA.2, C_RF.2, D2.2 (A), D4.2 (A), D5.2 (A), D8.2 (A), DTVS.2 (A), J2.A1 (GND), J2.A12 (GND), J2.B1 (GND), J2.B12 (GND), J2.SH (SHIELD), J3.2, J_CORE.2, J_CORE.4, J_CORE.6, J_CORE.19, J_CORE.20, J_SOL.2, Q1.1 (K), R1.2, R2.2, R_BEN_NC.2, R_FB2.2, R_HG.2, R_IG.2, R_PG2.2, R_RN.2, R_RTN.2, R_SH.2, U_BST.2 (GND), U_INA.1 (IN-3), U_INA.2 (IN+3), U_INA.3 (GND), U_INA.5 (A0), U_INA.17 (EP), U_INT.2 (VSS), U_INT.3 (IN+), U_MPPT.1 (GND), U_MPPT.4 (TEMP), U_RF.2 (GND)
I2C0_ALERT: J_CORE.17, U_INA.8 (WARNING)
I2C0_SCL: J_CORE.8, R_SCL.1, U_INA.6 (SCL)
I2C0_SDA: J_CORE.7, R_SDA.1, U_INA.7 (SDA)
INT_IN: C_INT.1, R_INT.2, U_INT.4 (IN-)
LED_A: D8.1 (K), R3.2
MPPT_C: C_MC.1, U_MPPT.5 (COMP)
PG_5V: J_CORE.14, R_PG.2, R_PG2.1
PT1000_RTN: J_CORE.15, J_RTD.2, R_RTN.1
ROGO_N: J_ROGO.2, R_RN.1
ROGO_P: J_ROGO.1, R_INT.1
SCR_G: D5.1 (K), Q1.3 (G), R5.2
SHIELD: J_CORE.18, R_SH.1
SOL_P: C_MP.1, J_SOL.1, U_MPPT.2 (VIN), U_MPPT.3 (CS), U_MPPT.8 (VCC)
VBUS: C3.1, D7.2 (A), J2.A4 (VBUS), J2.A9 (VBUS), J2.B4 (VBUS), J2.B9 (VBUS)
VHARV: D6.1 (K), D_HV.2 (A), R_HS.1, U_INA.14 (IN-2)
